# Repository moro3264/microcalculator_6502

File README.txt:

Microcalculator cu microprocesorul 6502 (WDC).

Scop
====

    Crearea unui sistem capabil sa gestioneze dispozitive auxiliare printr-un set
de functii de baza. Pe masura ce proiectul merge mai departe se vor dezvolta si alte capacitati software / hardware.

Impartirea memoriei
===================

        +-----------+
        |           |
        |           |
        |           |
        |           | 
        |    RAM    |   [0x0000, 0x7FFF] (32 KiB)
        |           |
        |           |
        |           |
        |           |
        |           |
        +-----------+
        |   ACIA    |   [0x8000, 0x800F] (16 B)
        +-----------+
        |   VIA     |   [0x8010, 0x801F] (16 B)
        +-----------+
        |   LIBER   |   [0x8020, 0x802F] (16 B)
        +-----------+
        |   LIBER   |   [0x8030, 0x803F] (16 B)
        +-----------+
        |           |
        |           |
        |           |
        |           |
        |    ROM    |   [0x8040, 0xFFFF] (32704 B)
        |           | 
        |           |
        |           |
        |           |
        +-----------+

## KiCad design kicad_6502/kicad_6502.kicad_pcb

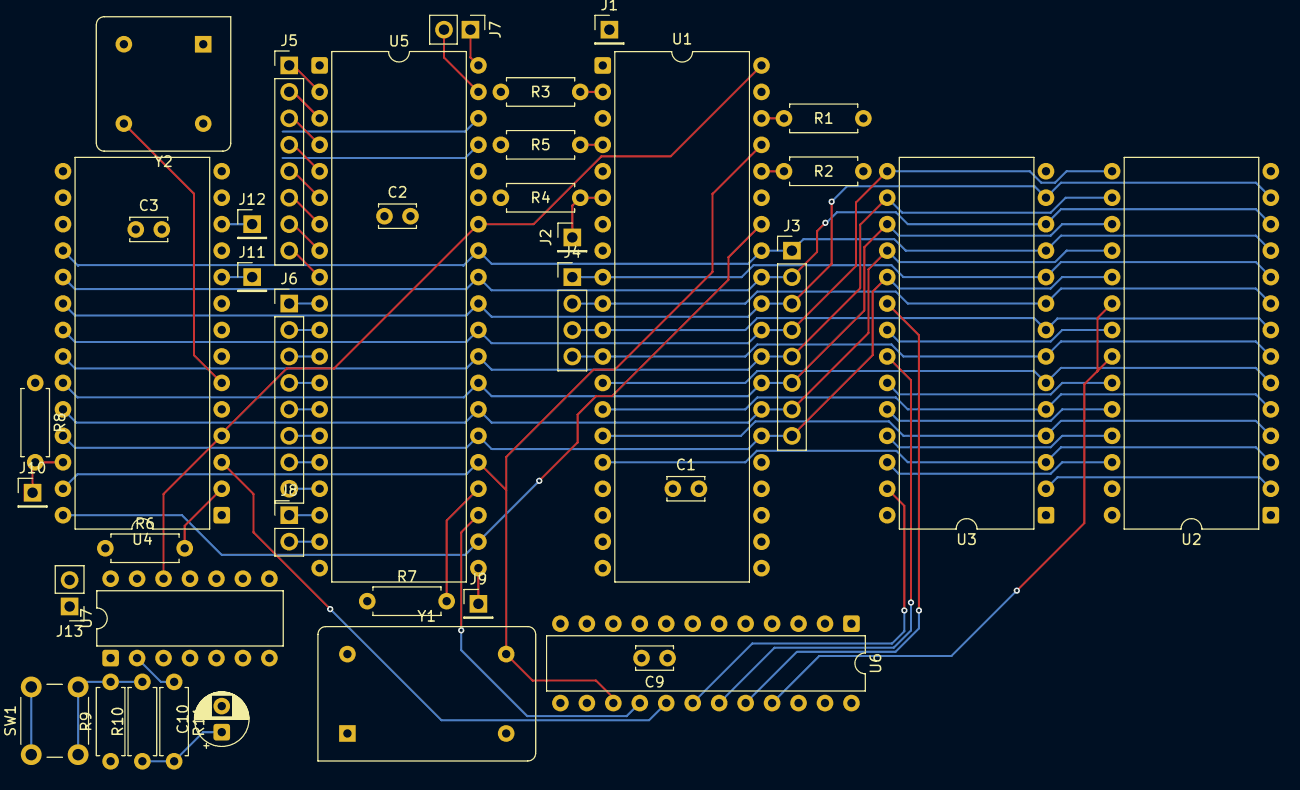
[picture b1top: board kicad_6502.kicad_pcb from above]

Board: 2 copper layers, 39 parts (0 on the bottom side), 70 nets.

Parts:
C1, C2, C3, C9: 0.1uF; C_Disc_D3.4mm_W2.1mm_P2.50mm
C10: 4.7uF; CP_Radial_D5.0mm_P2.50mm
J1: /IRQ; PinHeader_1x01_P2.54mm_Vertical
J2: /NMI; PinHeader_1x01_P2.54mm_Vertical
J3: D[7...0]; PinHeader_1x08_P2.54mm_Vertical
J4: A[3...0]; PinHeader_1x04_P2.54mm_Vertical
J5: PORTB; PinHeader_1x08_P2.54mm_Vertical
J6: PORTA; PinHeader_1x08_P2.54mm_Vertical
J7: CA; PinHeader_1x02_P2.54mm_Vertical
J8: CB; PinHeader_1x02_P2.54mm_Vertical
J9: /IRQ_VIA; PinHeader_1x01_P2.54mm_Vertical
J10: /IRQ_ACIA; PinHeader_1x01_P2.54mm_Vertical
J11: TX; PinHeader_1x01_P2.54mm_Vertical
J12: RX; PinHeader_1x01_P2.54mm_Vertical
J13: PWR; PinHeader_1x02_P2.54mm_Vertical
R1, R2, R3, R4, R5, R6, R7, R8, R9, R11: 5K; R_Axial_DIN0207_L6.3mm_D2.5mm_P7.62mm_Horizontal
R10: 250K; R_Axial_DIN0207_L6.3mm_D2.5mm_P7.62mm_Horizontal
SW1: RESET; SW_PUSH_6mm
U1: CPU; DIP-40_W15.24mm
U2: EEPROM; DIP-28_W15.24mm
U3: SRAM; DIP-28_W15.24mm
U4: ACIA; DIP-28_W15.24mm
U5: VIA; DIP-40_W15.24mm
U6: ATF22V10; DIP-24_W7.62mm
U7: 74LS73; DIP-14_W7.62mm
Y1: SYS_CLK; Oscillator_DIP-14
Y2: COM_CLK; Oscillator_DIP-8

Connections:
/+5V: C1.1, C2.1, C3.1, C9.1, J13.1, R1.1, R2.1, R3.1, R4.1, R5.1, R6.1, R7.1, R8.1, R9.1, U1.8 (VDD), U2.27 (~WE), U2.28 (VCC), U3.28 (VCC), U4.15 (VCC), U5.20 (VCC), U6.24 (VCC), U7.4 (VCC), U7.5 (C), U7.6 (~R), U7.7 (J), U7.10 (K), U7.14 (J), Y1.1 (EN), Y1.14 (Vcc), Y2.1 (EN), Y2.8 (Vcc)
/A0: J4.1, U1.9 (A0), U2.10 (A0), U3.10 (A0), U4.14 (RS1), U5.38 (RS0)
/A1: J4.2, U1.10 (A1), U2.9 (A1), U3.9 (A1), U4.13 (RS0), U5.37 (RS1)
/A2: J4.3, U1.11 (A2), U2.8 (A2), U3.8 (A2), U5.36 (RS2)
/A3: J4.4, U1.12 (A3), U2.7 (A3), U3.7 (A3), U5.35 (RS3)
/A4: U1.13 (A4), U2.6 (A4), U3.6 (A4), U6.13 (IN)
/A5: U1.14 (A5), U2.5 (A5), U3.5 (A5), U6.11 (IN)
/A6: U1.15 (A6), U2.4 (A6), U3.4 (A6), U6.10 (IN)
/A7: U1.16 (A7), U2.3 (A7), U3.3 (A7), U6.9 (IN)
/A8: U1.17 (A8), U2.25 (A8), U3.25 (A8), U6.8 (IN)
/A9: U1.18 (A9), U2.24 (A9), U3.24 (A9), U6.7 (IN)
/A10: U1.19 (A10), U2.21 (A10), U3.21 (A10), U6.6 (IN)
/A11: U1.20 (A11), U2.23 (A11), U3.23 (A11), U6.5 (IN)
/A12: U1.22 (A12), U2.2 (A12), U3.2 (A12), U6.4 (IN/PD)
/A13: U1.23 (A13), U2.26 (A13), U3.26 (A13), U6.3 (IN)
/A14: U1.24 (A14), U2.1 (A14), U3.1 (A14), U6.2 (IN)
/A15: U1.25 (A15), U6.1 (CLK/IN)
/COM_CLK: U4.6 (XTAL1), Y2.5 (OUT)
/D0: J3.1, U1.33 (D0), U2.11 (D0), U3.11 (Q0), U4.18 (D0), U5.33 (D0)
/D1: J3.2, U1.32 (D1), U2.12 (D1), U3.12 (Q1), U4.19 (D1), U5.32 (D1)
/D2: J3.3, U1.31 (D2), U2.13 (D2), U3.13 (Q2), U4.20 (D2), U5.31 (D2)
/D3: J3.4, U1.30 (D3), U2.15 (D3), U3.15 (Q3), U4.21 (D3), U5.30 (D3)
/D4: J3.5, U1.29 (D4), U2.16 (D4), U3.16 (Q4), U4.22 (D4), U5.29 (D4)
/D5: J3.6, U1.28 (D5), U2.17 (D5), U3.17 (Q5), U4.23 (D5), U5.28 (D5)
/D6: J3.7, U1.27 (D6), U2.18 (D6), U3.18 (Q6), U4.24 (D6), U5.27 (D6)
/D7: J3.8, U1.26 (D7), U2.19 (D7), U3.19 (Q7), U4.25 (D7), U5.26 (D7)
/R/W: U1.34 (R/~W), U4.28 (R/~W), U5.22 (R/~W), U6.14 (I/O)
/SYS_CLK: U1.37 (ϕ0), U4.27 (ϕ2), U5.25 (ϕ2), U6.15 (I/O), U7.1 (C), Y1.8 (OUT)
//CE_ACIA: U4.3 (~CS2), U6.17 (I/O)
//CE_RAM: U3.20 (~CS), U6.20 (I/O)
//CE_ROM: U2.20 (~CS), U2.22 (~OE), U6.21 (I/O)
//CE_VIA: U5.23 (~CS2), U6.16 (I/O)
//OE_RAM: U3.22 (~OE), U6.19 (I/O)
//RESET: U1.40 (~RES), U4.4 (~RES), U5.34 (~RES), U7.12 (Q)
//WE_RAM: U3.27 (~WE), U6.18 (I/O)
GNDD: C1.2, C2.2, C3.2, C9.2, C10.2, J13.2, SW1.1, U1.21 (VSS), U2.14 (GND), U3.14 (GND), U4.1 (VSS), U5.1 (VSS), U6.12 (GND), U7.3 (K), U7.11 (GND), Y1.7 (GND), Y2.4 (GND)
unnamed: C10.1, R10.1, R11.2
unnamed: J1.1 (Pin_1_1), R5.2, U1.4 (~IRQ)
unnamed: J2.1 (Pin_1_1), R4.2, U1.6 (~NMI)
unnamed: J5.1, U5.2 (PA0)
unnamed: J5.2, U5.3 (PA1)
unnamed: J5.3, U5.4 (PA2)
unnamed: J5.4, U5.5 (PA3)
unnamed: J5.5, U5.6 (PA4)
unnamed: J5.6, U5.7 (PA5)
unnamed: J5.7, U5.8 (PA6)
unnamed: J5.8, U5.9 (PA7)
unnamed: J6.1, U5.10 (PB0)
unnamed: J6.2, U5.11 (PB1)
unnamed: J6.3, U5.12 (PB2)
unnamed: J6.4, U5.13 (PB3)
unnamed: J6.5, U5.14 (PB4)
unnamed: J6.6, U5.15 (PB5)
unnamed: J6.7, U5.16 (PB6)
unnamed: J6.8, U5.17 (PB7)
unnamed: J7.1, U5.40 (CA1)
unnamed: J7.2, U5.39 (CA2)
unnamed: J8.1, U5.18 (CB1)
unnamed: J8.2, U5.19 (CB2)
unnamed: J9.1 (Pin_1_1), U5.21 (~IRQ)
unnamed: J10.1 (Pin_1_1), R8.2, U4.26 (~IRQ)
unnamed: J11.1 (Pin_1_1), U4.10 (TxD)
unnamed: J12.1 (Pin_1_1), U4.12 (RxD)
unnamed: R9.2, R10.2, SW1.2
unnamed: R2.2, U1.36 (BE)
unnamed: R3.2, U1.2 (RDY)
unnamed: R1.2, U1.38 (~SO)
unnamed: R6.2, U4.2 (CS1)
unnamed: R7.2, U5.24 (CS1)
unnamed: R11.1, U7.2 (~R)

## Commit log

2026-05-09 init
2026-05-09 schimbari makefile
2026-05-09 test
2026-05-09 schimbari la numele unor variabile
2026-05-10 kicad dir adaugat
2026-05-10 makefile modificat
2026-05-10 makefile actualizat
2026-05-11 fisiere kicad
2026-05-11 fisiere create pentru controlul perifericelor
2026-05-11 eliminare LCD_INIT
2026-05-11 LCD-ul nu va mai face parte din sistem dar va putea fi controlat in caz ca este conectat la placa
2026-05-11 README.txt
2026-05-11 del README.md
2026-05-12 schimbari pentru harta de memorie
2026-05-12 altele
2026-05-13 mici schimbari
2026-05-13 Altele. Sper ca de acuma sa fie gata setupu la workflow
2026-05-13 readme actualizat
2026-05-15 f pentru ATF22V10
2026-05-15 diagrama actualizata
2026-05-15 schimbare poza
2026-05-15 corectare readme
2026-05-16 actualizare fisier pld
2026-05-16 mici schimbari si adaugiri
2026-05-17 breadboard
2026-05-17 RAM: sincronizare cu PHI2
2026-05-17 test de functionare
2026-05-17 redenumire
2026-05-17 adaugare comanda pentru compilare fisier pentru pld
2026-05-20 schimbari + testare conexiune ACIA <-> PC
2026-05-20 corectare
2026-05-22 inceput de logica pentru incarcarea programelor prin UART
2026-05-24 schimbari kicad
